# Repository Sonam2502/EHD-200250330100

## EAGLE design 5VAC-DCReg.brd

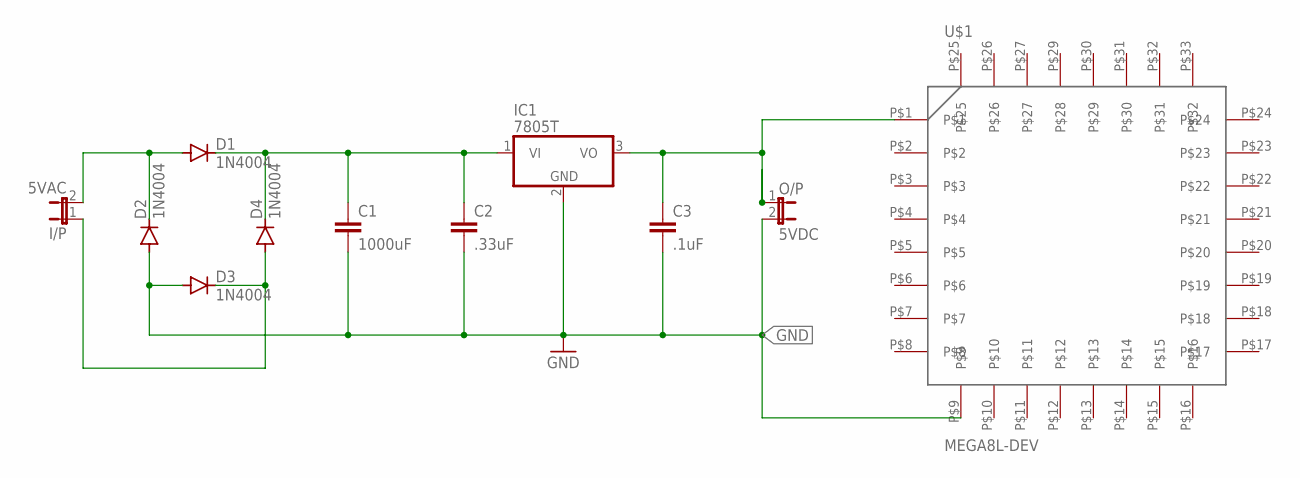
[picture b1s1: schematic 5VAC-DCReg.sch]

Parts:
C1: 1000uF; C2.5-3
C2: .33uF; C2.5-3
C3: .1uF; C2.5-3
D1, D2, D3, D4: 1N4004; DO41-10
I/P: 5VAC; JP1
IC1: 7805T; TO220H
O/P: 5VDC; JP1
U$1: MEGA8L-DEV; TQFP-MEGA8L

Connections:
GND: C1.2, C2.2, C3.2, D2.A, D3.A, IC1.2 (GND), O/P.2, U$1.P$9
unnamed: D3.C, D4.A, I/P.1
unnamed: C3.1, IC1.3 (VO), O/P.1, U$1.P$1
unnamed: D1.A, D2.C, I/P.2
unnamed: C1.1, C2.1, D1.C, D4.C, IC1.1 (VI)

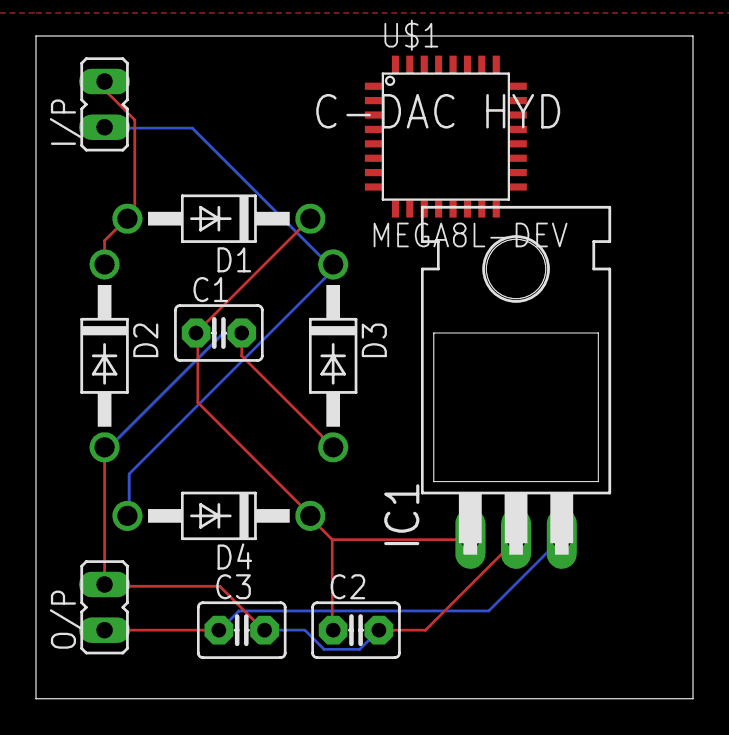
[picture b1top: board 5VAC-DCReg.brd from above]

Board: 2 copper layers, 36.5 x 36.8 mm, 11 parts (0 on the bottom side), 5 nets.
